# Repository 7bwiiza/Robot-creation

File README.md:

# Robot-creation
Uni project of a 3D model of a 5dof robot using Solidedge and motor control using KiCAD and MATLAB

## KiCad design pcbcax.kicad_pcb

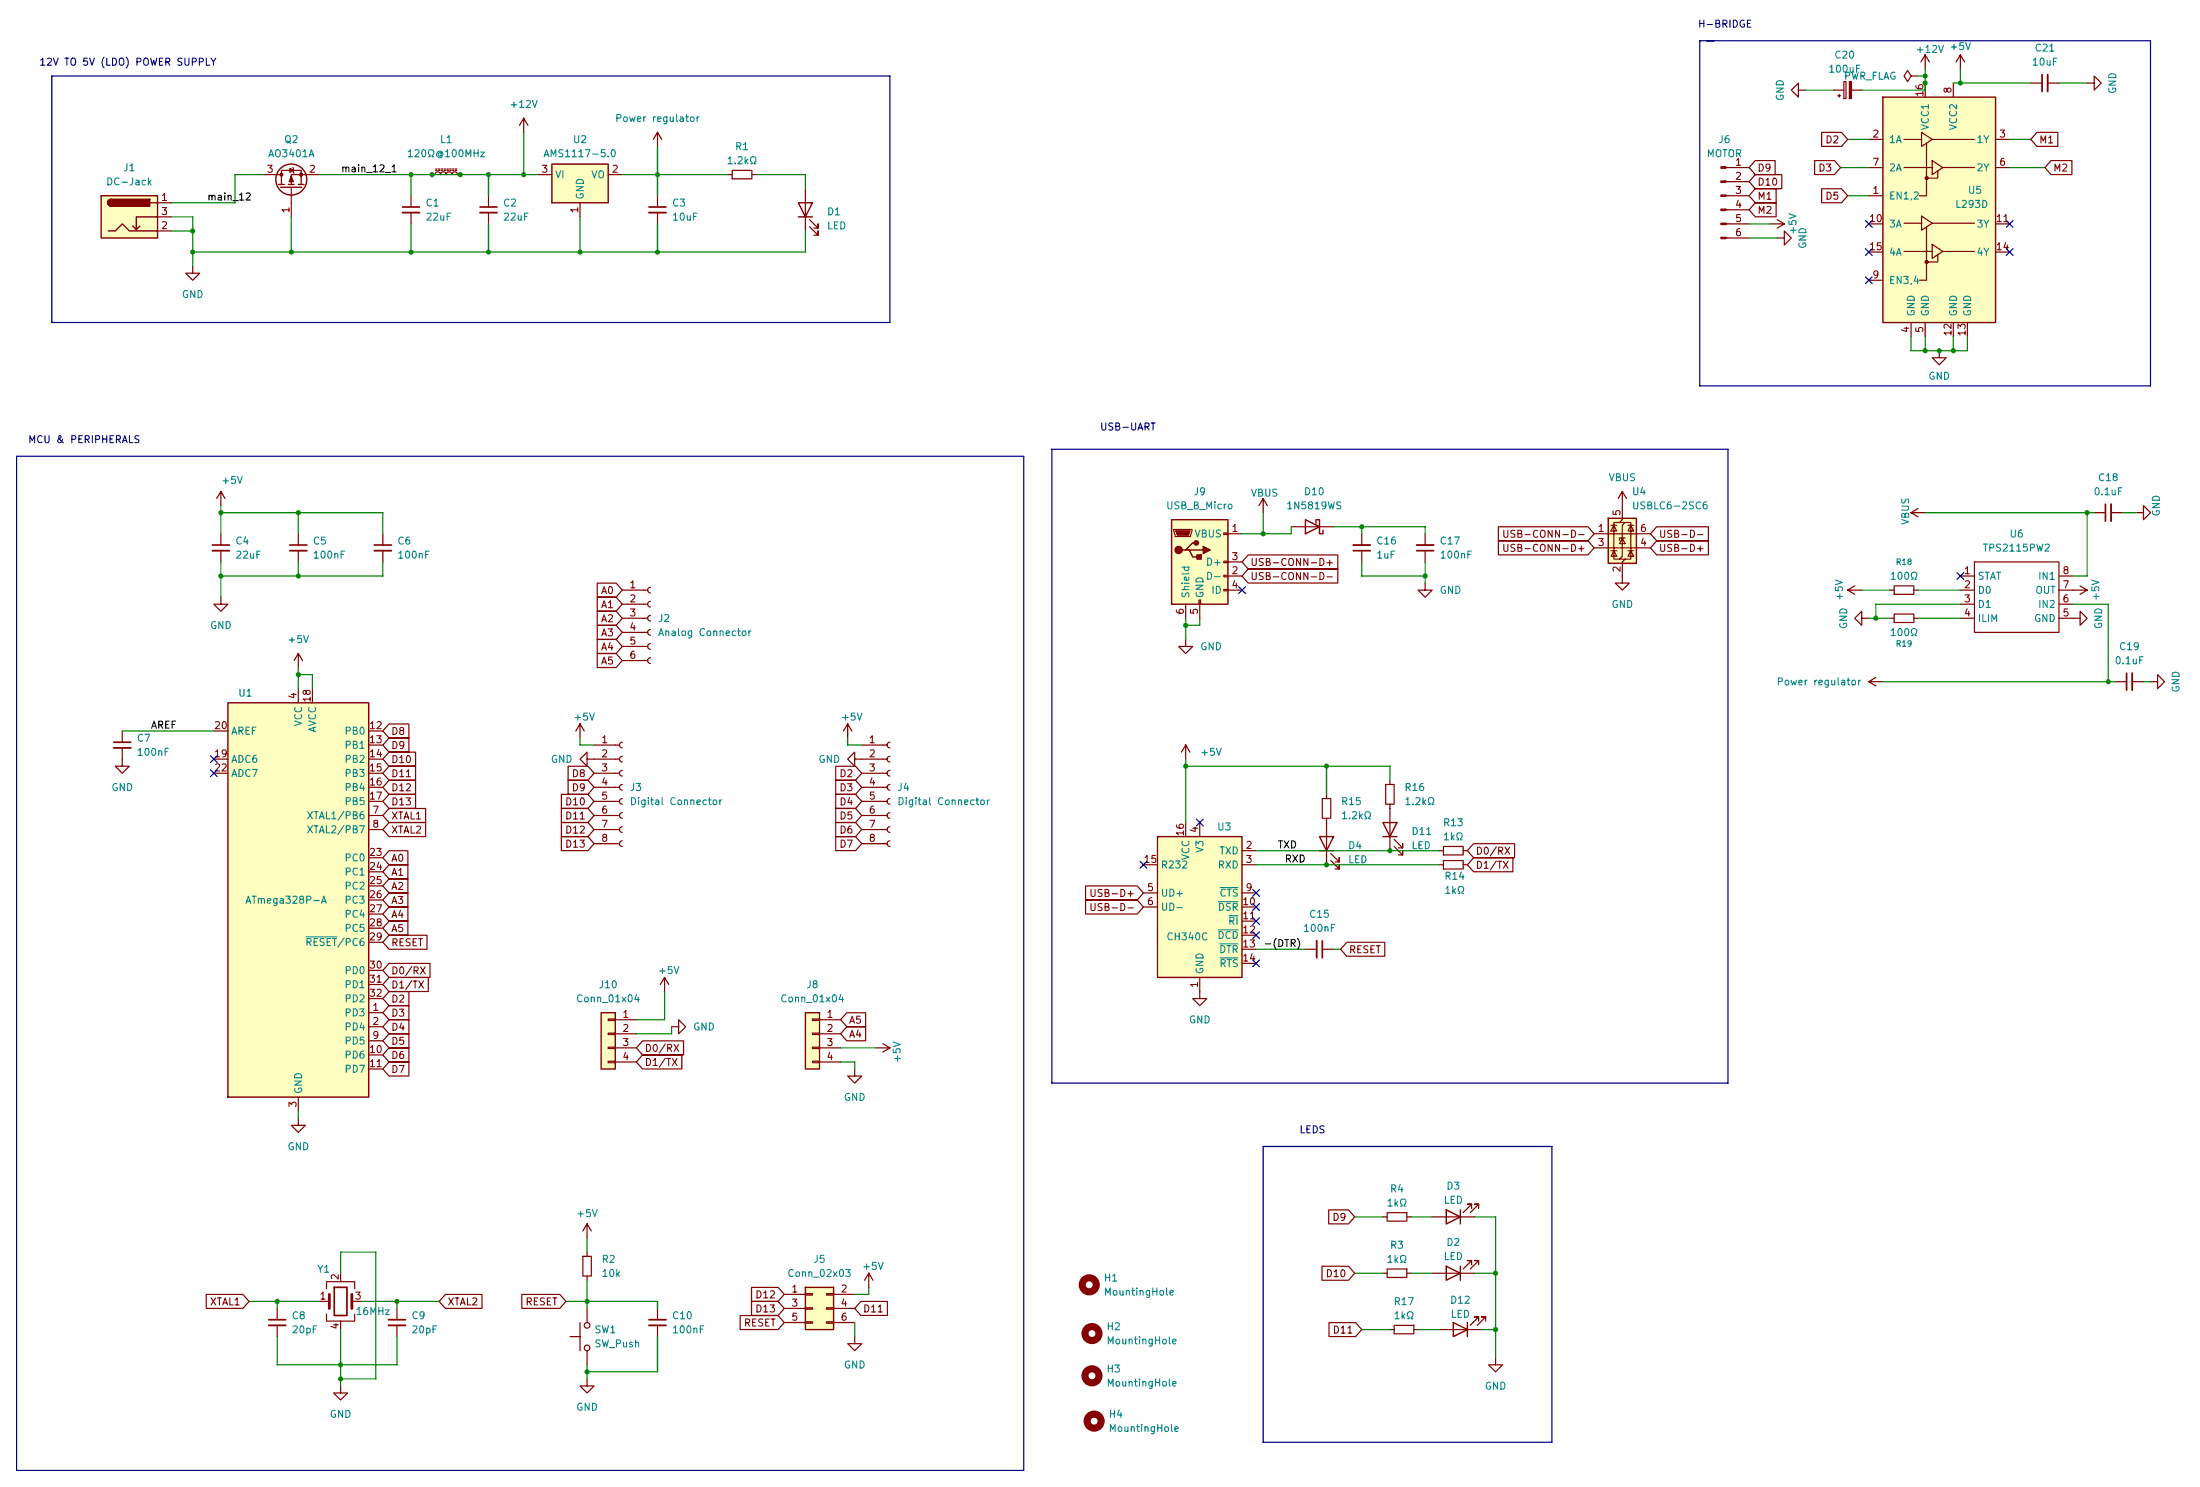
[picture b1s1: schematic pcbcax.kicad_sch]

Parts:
C1, C2, C4: 22uF; C_0805_2012Metric
C3: 10uF; C_0805_2012Metric
C5, C6, C7, C10, C15, C17: 100nF; C_0603_1608Metric
C8, C9: 20pF; C_0603_1608Metric
C16: 1uF; C_0603_1608Metric
C18, C19: 0.1uF; C_0603_1608Metric
C20: 100uF; CP_Elec_8x10.5
C21: 10uF; C_0603_1608Metric
D1, D2, D3, D4, D11, D12: LED; LED_0603_1608Metric
D10: 1N5819WS; D_SOD-323
H1, H2, H3, H4: MountingHole; MountingHole_2.1mm
J1: DC-Jack; BarrelJack_Wuerth_6941xx301002
J2: Analog Connector; PinSocket_1x06_P1.27mm_Vertical
J3, J4: Digital Connector; PinSocket_1x08_P1.27mm_Vertical
J5: Conn_02x03; PinHeader_2x03_P2.54mm_Vertical
J6: MOTOR; TerminalBlock_Phoenix_MKDS-1,5-6_1x06_P5.00mm_Horizontal
J8, J10: Conn_01x04; PinHeader_1x04_P2.54mm_Vertical
J9: USB_B_Micro; USB_Micro-B_Molex_47346-0001
L1: 120Ω@100MHz; L_0805_2012Metric
Q2: AO3401A; SOT-23
R1, R15, R16: 1.2kΩ; R_0603_1608Metric
R2: 10k; R_0603_1608Metric
R3, R4, R13, R14, R17: 1kΩ; R_0603_1608Metric
R18, R19: 100Ω; R_0603_1608Metric
SW1: SW_Push; SW_PUSH_6mm_H4.3mm
U1: ATmega328P-A; TQFP-32_7x7mm_P0.8mm
U2: AMS1117-5.0; SOT-223-3_TabPin2
U3: CH340C; SOIC-16_3.9x9.9mm_P1.27mm
U4: USBLC6-2SC6; SOT-23-6
U5: L293D; DIP-16_W7.62mm
U6: TPS2115PW2; TSSOP-8_3x3mm_P0.65mm
Y1: 16MHz; Crystal_SMD_3225-4Pin_3.2x2.5mm

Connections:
+5V: C4.1, C5.1, C6.1, C21.1, J3.1, J4.1, J5.2, J6.5, J8.3, J10.1, R2.1, R15.1, R16.1, R18.1, U1.4 (VCC), U1.6 (VCC), U1.18 (AVCC), U3.16 (VCC), U5.8 (VCC2), U6.7 (OUT)
+12V: C1.1, C2.1, C20.2, L1.1, L1.2, Q2.2 (S), U2.3 (VI), U5.16 (VCC1)
/-(DTR): C15.2, U3.13 (~DTR)
/AREF: C7.1, U1.20 (AREF)
/RXD: D4.1 (K), R14.1, U3.3 (RXD)
/TXD: D11.1 (K), R13.1, U3.2 (TXD)
/main_12: J1.1, Q2.3 (D)
A0: J2.1, U1.23 (PC0)
A1: J2.2, U1.24 (PC1)
A2: J2.3, U1.25 (PC2)
A3: J2.4, U1.26 (PC3)
A4: J2.5, J8.2, U1.27 (PC4)
A5: J2.6, J8.1, U1.28 (PC5)
D0/RX: J10.3, R13.2, U1.30 (PD0)
D1/TX: J10.4, R14.2, U1.31 (PD1)
D2: J4.3, U1.32 (PD2), U5.2 (1A)
D3: J4.4, U1.1 (PD3), U5.7 (2A)
D4: J4.5, U1.2 (PD4)
D5: J4.6, U1.9 (PD5), U5.1 (EN1,2)
D6: J4.7, U1.10 (PD6)
D7: J4.8, U1.11 (PD7)
D8: J3.3, U1.12 (PB0)
D9: J3.4, J6.1, R4.2, U1.13 (PB1)
D10: J3.5, J6.2, R3.2, U1.14 (PB2)
D11: J3.6, J5.4, R17.2, U1.15 (PB3)
D12: J3.7, J5.1, U1.16 (PB4)
D13: J3.8, J5.3, U1.17 (PB5)
GND: C1.2, C2.2, C3.2, C4.2, C5.2, C6.2, C7.2, C8.2, C9.2, C10.2, C16.1, C17.1, C18.2, C19.2, C20.1, C21.2, D1.1 (K), D2.1 (K), D3.1 (K), D12.1 (K), J1.2, J1.3, J3.2, J4.2, J5.6, J6.6, J8.4, J9.5 (GND), J9.6 (Shield), J10.2, Q2.1 (G), R19.1, SW1.1, U1.3 (GND), U1.5 (GND), U1.21 (GND), U2.1 (GND), U3.1 (GND), U4.2 (GND), U5.4 (GND), U5.5 (GND), U5.12 (GND), U5.13 (GND), U6.3 (D1), U6.5 (GND), Y1.2, Y1.4
M1: J6.3, U5.3 (1Y)
M2: J6.4, U5.6 (2Y)
unnamed: D1.2 (A), R1.2
unnamed: D2.2 (A), R3.1
unnamed: D3.2 (A), R4.1
unnamed: D4.2 (A), R15.2
unnamed: C16.2, C17.2, D10.1 (K)
unnamed: D11.2 (A), R16.2
unnamed: D12.2 (A), R17.1
unnamed: R18.2, U6.2 (D0)
unnamed: R19.2, U6.4 (ILIM)
Power regulator: C3.1, C19.1, R1.1, U2.2 (VO), U6.6 (IN2)
RESET: C10.1, C15.1, J5.5, R2.2, SW1.2, U1.29 (~RESET/PC6)
USB-CONN-D+: J9.3 (D+), U4.3 (I/O2)
USB-CONN-D-: J9.2 (D-), U4.1 (I/O1)
USB-D+: U3.5 (UD+), U4.4 (I/O2)
USB-D-: U3.6 (UD-), U4.6 (I/O1)
VBUS: C18.1, D10.2 (A), J9.1 (VBUS), U4.5 (VBUS), U6.8 (IN1)
XTAL1: C8.1, U1.7 (XTAL1/PB6), Y1.1
XTAL2: C9.1, U1.8 (XTAL2/PB7), Y1.3

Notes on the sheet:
H-BRIDGE
LEDS
12V TO 5V (LDO) POWER SUPPLY
USB-UART
MCU & PERIPHERALS

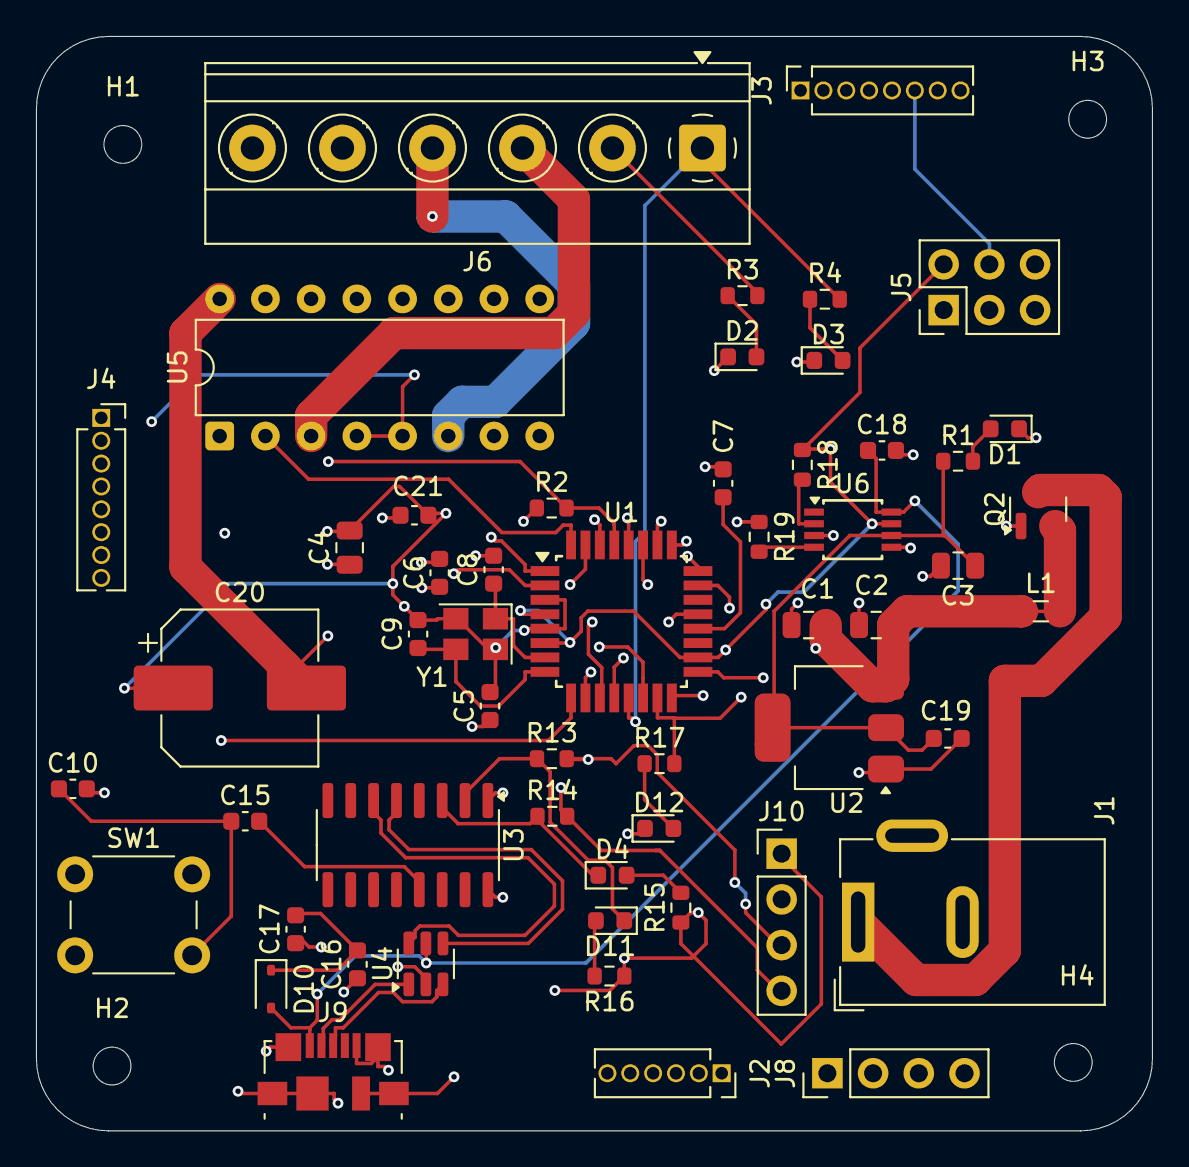
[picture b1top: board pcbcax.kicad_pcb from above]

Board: 4 copper layers, 62.0 x 60.8 mm, 58 parts (0 on the bottom side), 48 nets.
